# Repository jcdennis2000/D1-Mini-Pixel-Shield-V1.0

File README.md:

# D1-Mini-Pixel-Shield-V1.0

The D1 Mini Pixel Shield allows you to add some light to your WiFi projects!
The shield contains 9 WS2812B LEDs, commonly known as Neo Pixels. These are arranged in a 3x3 grid, allowing you to make some basic shapes. These pixels run at 5V, and are connected to the D4 pin on the D1 Mini.

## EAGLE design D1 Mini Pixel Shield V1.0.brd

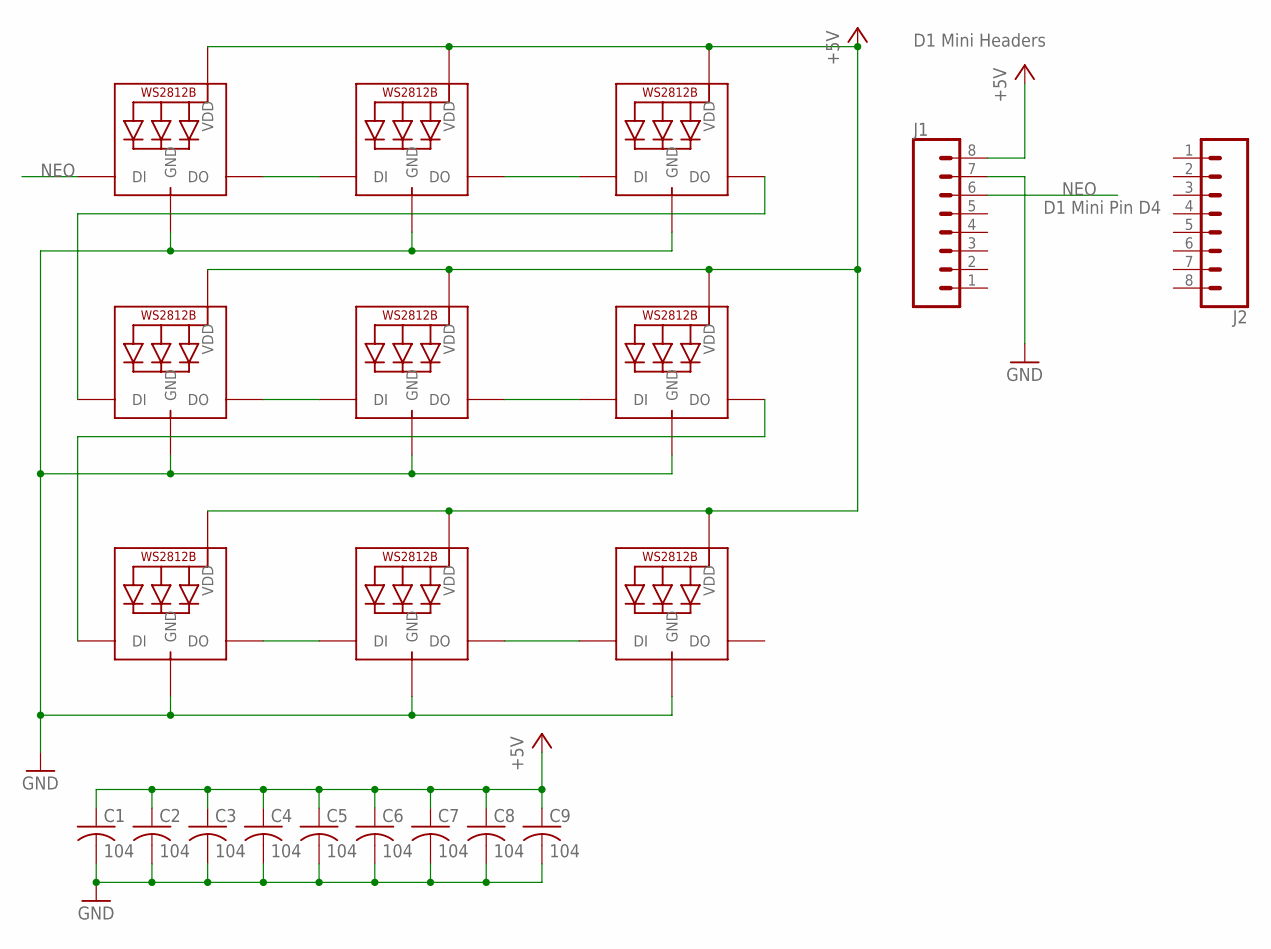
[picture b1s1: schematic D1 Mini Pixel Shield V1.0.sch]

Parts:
C1, C2, C3, C4, C5, C6, C7, C8, C9: 104; C0603
J1, J2: CONN_08"; 1X08
LED1, LED2, LED3, LED4, LED5, LED6, LED7, LED8, LED9: WS2812B_5050N; WS2812B-NARROW

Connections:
+5V: C1.1, C2.1, C3.1, C4.1, C5.1, C6.1, C7.1, C8.1, C9.1, J1.8, LED1.1-VDD (VDD), LED2.1-VDD (VDD), LED3.1-VDD (VDD), LED4.1-VDD (VDD), LED5.1-VDD (VDD), LED6.1-VDD (VDD), LED7.1-VDD (VDD), LED8.1-VDD (VDD), LED9.1-VDD (VDD)
GND: C1.2, C2.2, C3.2, C4.2, C5.2, C6.2, C7.2, C8.2, C9.2, J1.7, LED1.3-GND (GND), LED2.3-GND (GND), LED3.3-GND (GND), LED4.3-GND (GND), LED5.3-GND (GND), LED6.3-GND (GND), LED7.3-GND (GND), LED8.3-GND (GND), LED9.3-GND (GND)
unnamed: LED1.2-DOUT (DO), LED2.4-DIN (DI)
unnamed: LED2.2-DOUT (DO), LED3.4-DIN (DI)
unnamed: LED4.2-DOUT (DO), LED5.4-DIN (DI)
unnamed: LED5.2-DOUT (DO), LED6.4-DIN (DI)
unnamed: LED7.2-DOUT (DO), LED8.4-DIN (DI)
unnamed: LED8.2-DOUT (DO), LED9.4-DIN (DI)
unnamed: LED3.2-DOUT (DO), LED4.4-DIN (DI)
unnamed: LED6.2-DOUT (DO), LED7.4-DIN (DI)
NEO: J1.6, LED1.4-DIN (DI)

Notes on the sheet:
D1 Mini Pin D4
D1 Mini Headers

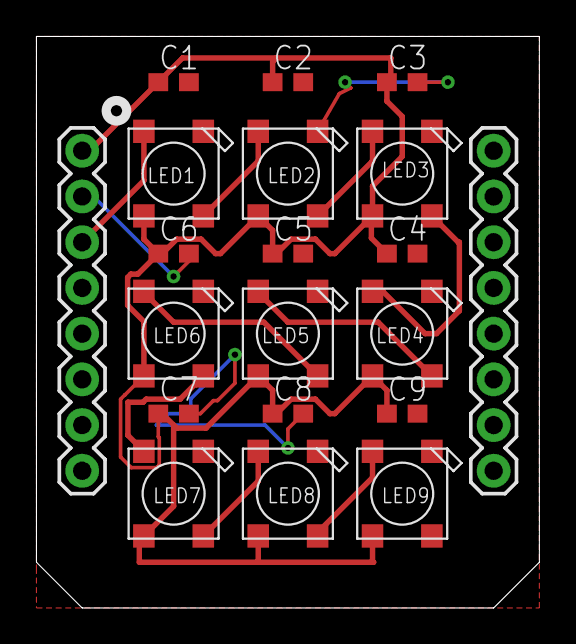
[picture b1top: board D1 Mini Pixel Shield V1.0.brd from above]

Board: 2 copper layers, 27.9 x 31.8 mm, 20 parts (0 on the bottom side), 11 nets.

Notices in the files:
D1 Mini Pixel Shield V1.0.brd:
Dennistries Ltd (c) 2019
parts and their libraries:
SparkFun-Connectors: Licensing: Creative Commons ShareAlike 4.0 International - https://creativecommons.org/licenses/by-sa/4.0
